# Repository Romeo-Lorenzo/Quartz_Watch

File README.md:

# DIY Quartz Watch project

## Introduction
This is my take at making my own quartz watch with a twist.
Driven by a PCF2003 chip from NXP as well as an STM32WB for bluetooth capability and controlling the subdial driving system in order to display data from the equipped sensors:
- Barometer
- Compass
- VBat
- Temp
- 1 cell lithium charge and discharge
- Very low power circuitry, 150nA continuous current consumption and 150mA with STM32 turned on. Designed to be equipped of two Airpods1 batteries in parralel for 50mAh total.

##Hardware:

  The hardware is divided into electrical and mecanical hardware

  ###Electrical:
  - 6 layer 36mm PCB board designed to replace original PCB from a Miyota 2035 movement. The PCB has two contact pads for two Miyota 2035 movements to drive both main and sub-dial. It is equipped with contact pads to ease programming of both the STM32 and the PCF 2003, most likely with pogo pin alignement 3D print to come.

  - TODO Monolayer PCB to mount as shield on Nucleo board equipped with OP Amp to be able to output the voltage necessary to program the PCF 2003. Will most likely be designed as a programming station and include the pogo pins and debug connector for programming the STM32 as well and be integrated with the forementioned 3d model to print.
 
  ###Mecanical:
  - Onshape designed 36mm watch case with high water resistance in mind, a water tight push button to control subdial and STM32 ON time.

Note that the Miyota 2035 movements will have to be modified, taking it apart and filing away the excess material on the bottom holding plate for the subdial movement is an easy fit and a tutorial on how to take apart and prepare the movements will be released.
The case is not yet finished but I estimate a 5 atm water tight watch, tolerances for CNC machinig will have to be tested. Crown will be a screw-in watertight type, a silicon membrane will ensure watertightness of the push button all the while allowing the inside barometer to read pressure, especially fun underwater.

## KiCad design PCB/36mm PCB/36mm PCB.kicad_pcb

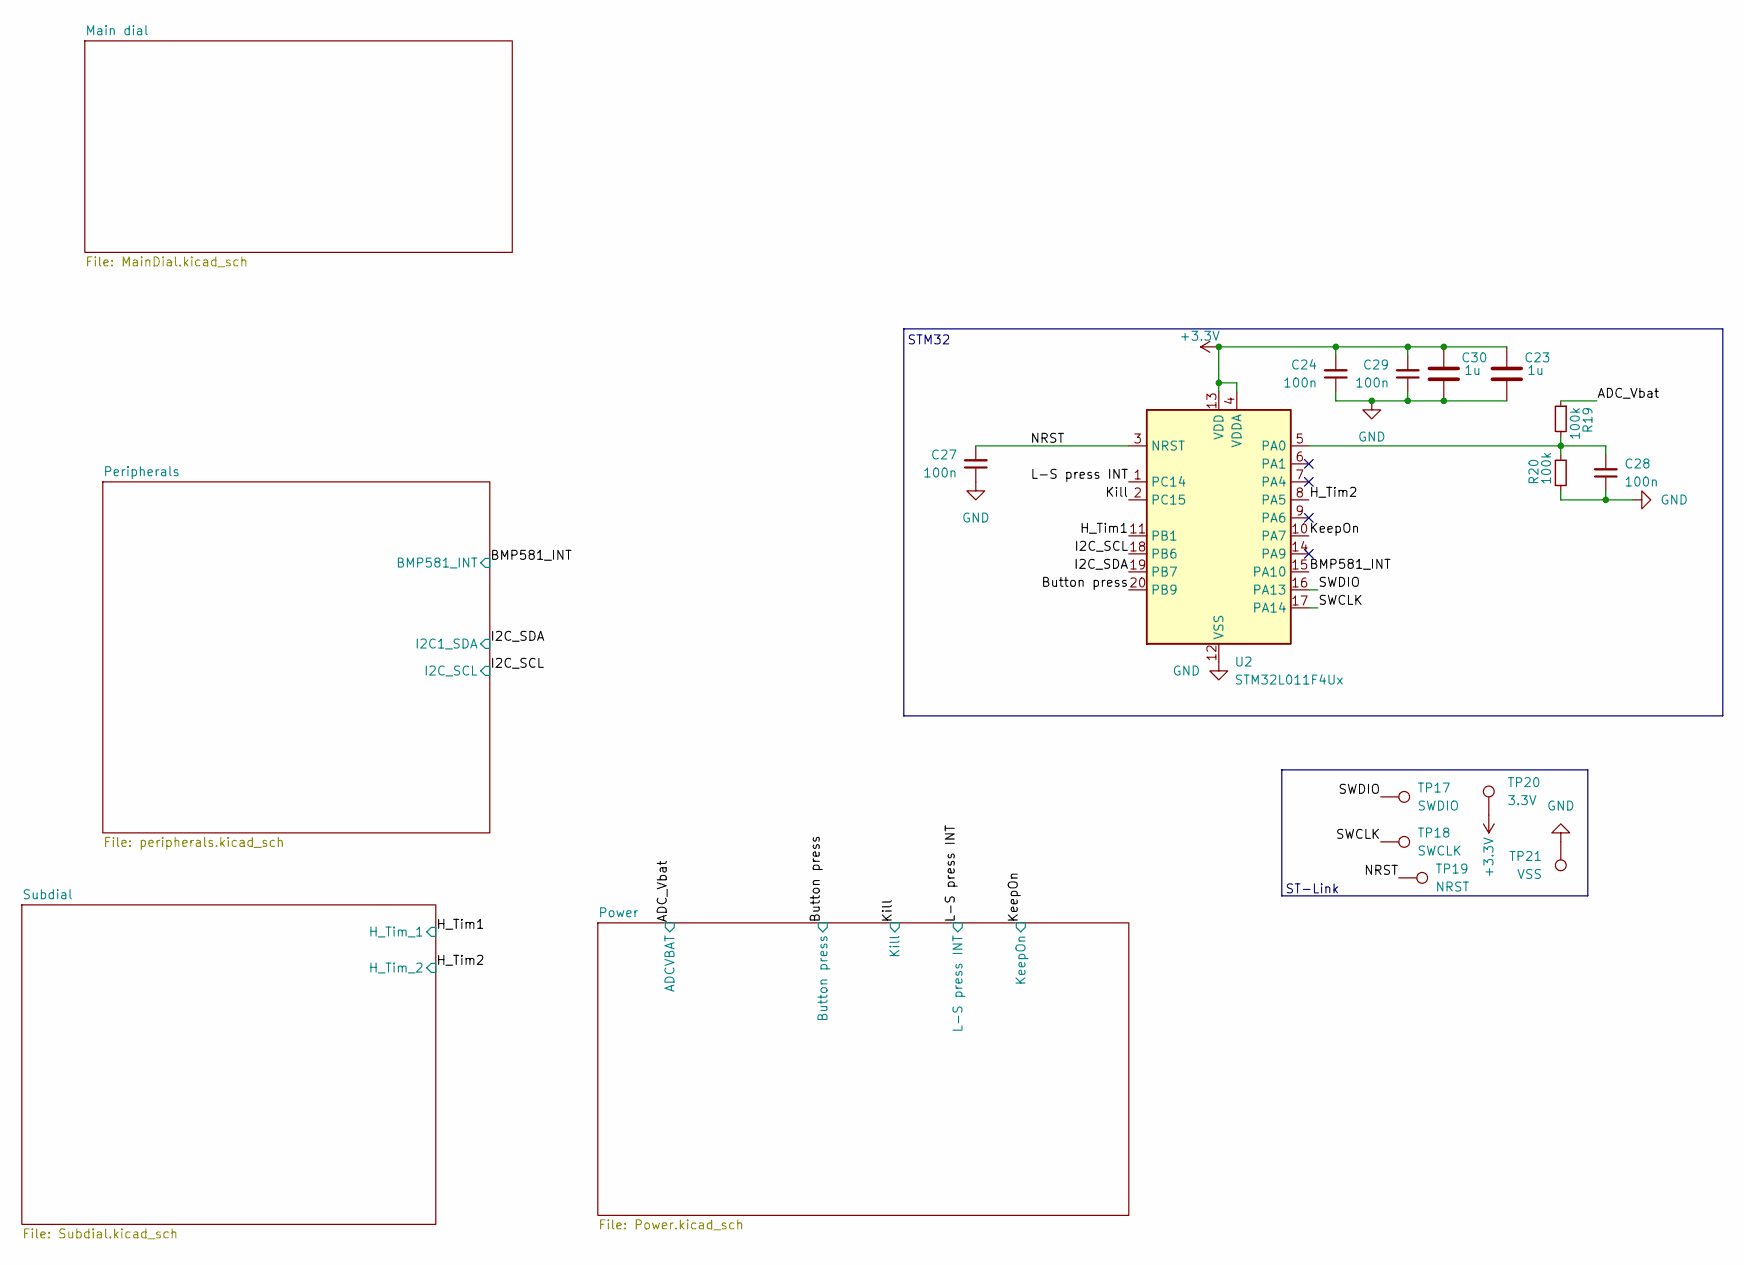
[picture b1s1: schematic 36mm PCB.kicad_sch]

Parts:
C23, C30: 1u; C_0402_1005Metric
C24, C27, C28, C29: 100n; C_0201_0603Metric
R19, R20: 100k; R_0201_0603Metric
TP17: SWDIO; Pogo pin 1x1
TP18: SWCLK; Pogo pin 1x1
TP19: NRST; Pogo pin 1x1
TP20: 3.3V; Pogo pin 1x1
TP21: VSS; Pogo pin 1x1
U2: STM32L011F4Ux; ST_UFQFPN-20_3x3mm_P0.5mm

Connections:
+3.3V: C23.1, C24.2, C29.2, C30.1, TP20.1, U2.4 (VDDA), U2.13 (VDD); also elsewhere on the board
+3V0: R19.1; also elsewhere on the board
/BMP581_INT: U2.15 (PA10); also elsewhere on the board
/Button press: U2.20 (PB9); also elsewhere on the board
/H_Tim1: U2.11 (PB1); also elsewhere on the board
/H_Tim2: U2.8 (PA5); also elsewhere on the board
/I2C_SCL: U2.18 (PB6); also elsewhere on the board
/I2C_SDA: U2.19 (PB7); also elsewhere on the board
/KeepOn: U2.10 (PA7); also elsewhere on the board
/Kill: U2.2 (PC15); also elsewhere on the board
/L-S press INT: U2.1 (PC14); also elsewhere on the board
/NRST: C27.2, TP19.1, U2.3 (NRST)
/SWCLK: TP18.1, U2.17 (PA14)
/SWDIO: TP17.1, U2.16 (PA13)
GND: C23.2, C24.1, C27.1, C28.1, C29.1, C30.2, R20.1, TP21.1, U2.12 (VSS); also elsewhere on the board
unnamed: C28.2, R19.2, R20.2, U2.5 (PA0)

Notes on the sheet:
ST-Link
STM32

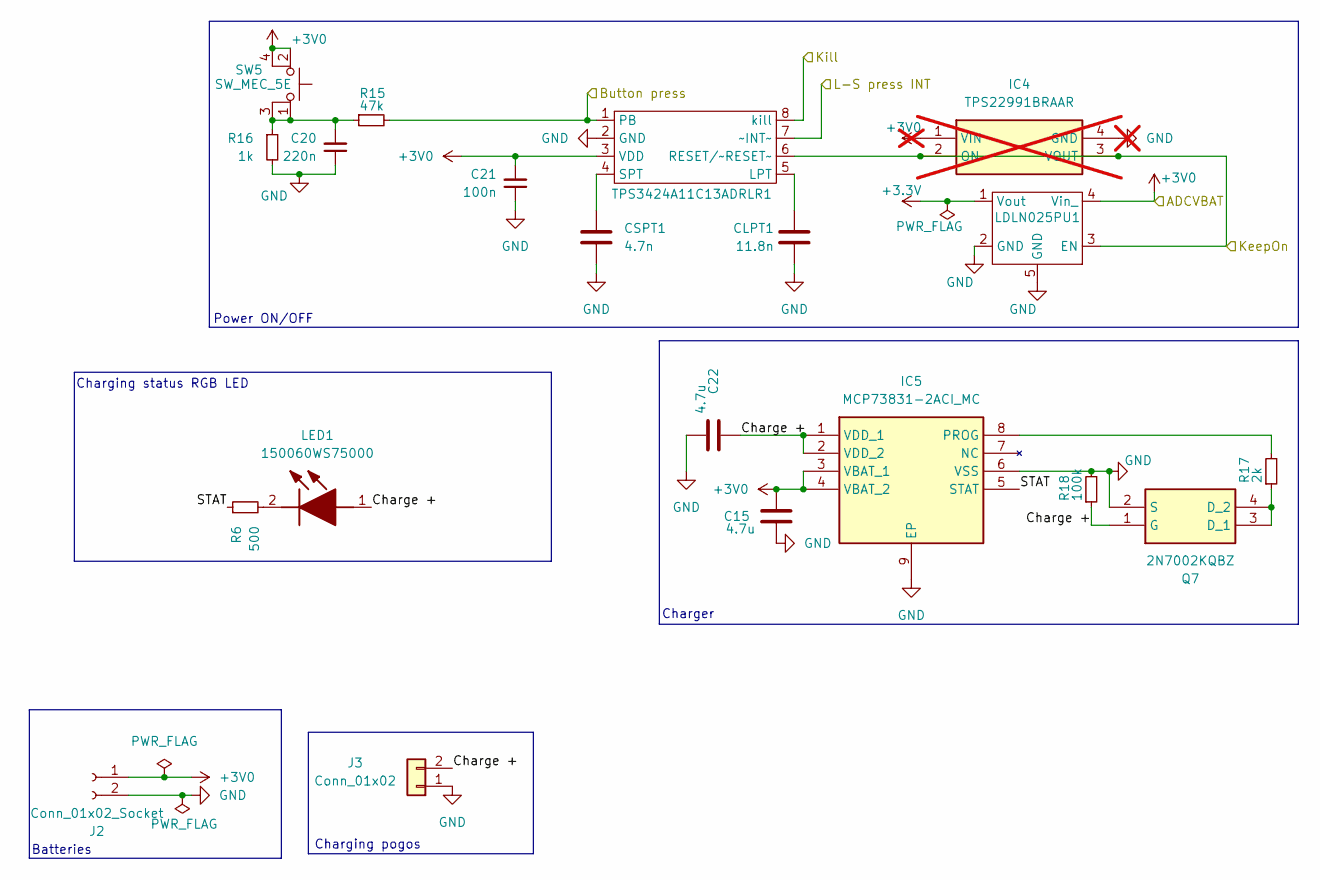
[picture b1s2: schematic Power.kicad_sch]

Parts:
C15, C22: 4.7u; C_0402_1005Metric
C20: 220n; C_0201_0603Metric
C21: 100n; C_0201_0603Metric
CLPT1: 11.8n; C_0402_1005Metric
CSPT1: 4.7n; C_0402_1005Metric
IC4: TPS22991BRAAR; Manufacturer_Part_Number TPS22991BRAAR; Mouser Part Number 595-TPS22991BRAAR; not fitted
IC5: MCP73831-2ACI_MC; SON50P300X200X100-9N-D; Manufacturer_Part_Number MCP73831-2ACI/MC; Mouser Part Number 579-MCP73831-2ACI/MC
J2: Conn_01x02_Socket; Battery 36mm watch
J3: Conn_01x02; Battery pogo pins
LDLN025PU1: OnSemi_XDFN4-1EP_1.0x1.0mm_EP0.52x0.52mm
LED1: 150060WS75000; Manufacturer_Part_Number 150060WS75000; Mouser Part Number 710-150060WS75000
Q7: 2N7002KQBZ; Manufacturer_Part_Number 2N7002KQBZ; Mouser Part Number 771-2N7002KQBZ
R6: 500; R_0201_0603Metric
R15: 47k; R_0201_0603Metric
R16: 1k; R_0201_0603Metric
R17: 2k; R_0201_0603Metric
R18: 100k; R_0201_0603Metric
SW5: SW_MEC_5E; Wurth side button 434331013822
TPS3424A11C13ADRLR1: SOT-583-8

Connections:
+3.3V: LDLN025PU1.1 (Vout); also elsewhere on the board
+3V0: C15.1, C21.2, IC4.1 (VIN), IC5.3 (VBAT_1), IC5.4 (VBAT_2), J2.1, LDLN025PU1.4 (Vin_), SW5.2, SW5.4, TPS3424A11C13ADRLR1.3 (VDD); also elsewhere on the board
/Button press: R15.2, TPS3424A11C13ADRLR1.1 (PB); also elsewhere on the board
/KeepOn: IC4.2 (ON), IC4.3 (VOUT), LDLN025PU1.3 (EN), TPS3424A11C13ADRLR1.6 (RESET/~RESET~); also elsewhere on the board
/Kill: TPS3424A11C13ADRLR1.8 (kill); also elsewhere on the board
/L-S press INT: TPS3424A11C13ADRLR1.7 (~INT~); also elsewhere on the board
/Power/Charge +: C22.1, IC5.1 (VDD_1), IC5.2 (VDD_2), J3.2, LED1.1 (A), Q7.1 (G), R18.1
/Power/STAT: IC5.5 (STAT), R6.1
GND: C15.2, C20.1, C21.1, C22.2, CLPT1.1, CSPT1.1, IC4.4 (GND), IC5.6 (VSS), IC5.9 (EP), J2.2, J3.1, LDLN025PU1.2 (GND), LDLN025PU1.5 (GND), Q7.2 (S), R16.2, R18.2, TPS3424A11C13ADRLR1.2 (GND); also elsewhere on the board
unnamed: C20.2, R15.1, R16.1, SW5.1, SW5.3
unnamed: IC5.8 (PROG), R17.2
unnamed: LED1.2 (K), R6.2
unnamed: Q7.3 (D_1), Q7.4 (D_2), R17.1
unnamed: CLPT1.2, TPS3424A11C13ADRLR1.5 (LPT)
unnamed: CSPT1.2, TPS3424A11C13ADRLR1.4 (SPT)

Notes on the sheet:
Charging pogos
Charging status RGB LED
Charger
Batteries
Power ON/OFF

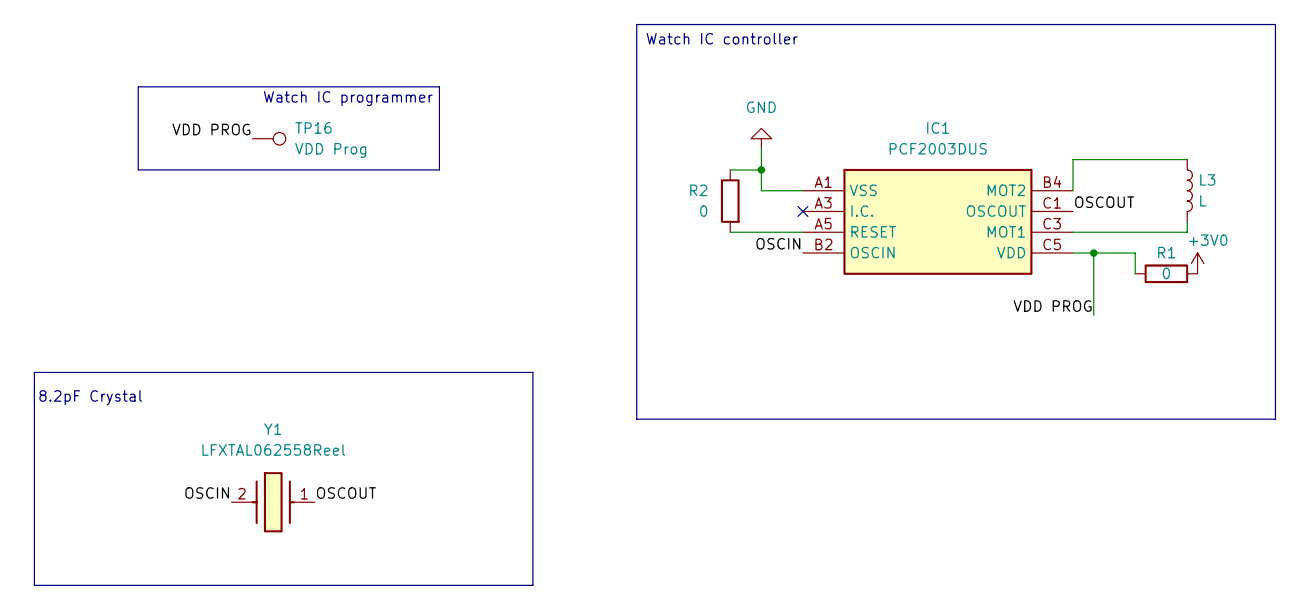
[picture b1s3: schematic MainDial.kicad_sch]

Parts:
IC1: PCF2003DUS; Manufacturer_Part_Number PCF2003DUS
L3: L; Miyota 2035
R1, R2: 0; R_0201_0603Metric
TP16: VDD Prog; Pogo pin 1x1
Y1: LFXTAL062558Reel; Manufacturer_Part_Number LFXTAL062558Reel; Mouser Part Number 449-LFXTAL062558REEL

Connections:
+3V0: R1.2; also elsewhere on the board
/Main dial/OSCIN: IC1.B2 (OSCIN), Y1.2 (CRYSTAL_2)
/Main dial/OSCOUT: IC1.C1 (OSCOUT), Y1.1
/Main dial/VDD PROG: IC1.C5 (VDD), R1.1, TP16.1
GND: IC1.A1 (VSS), R2.1; also elsewhere on the board
unnamed: IC1.C3 (MOT1), L3.2
unnamed: IC1.B4 (MOT2), L3.1
unnamed: IC1.A5 (RESET), R2.2

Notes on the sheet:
Watch IC controller
Watch IC programmer
8.2pF Crystal

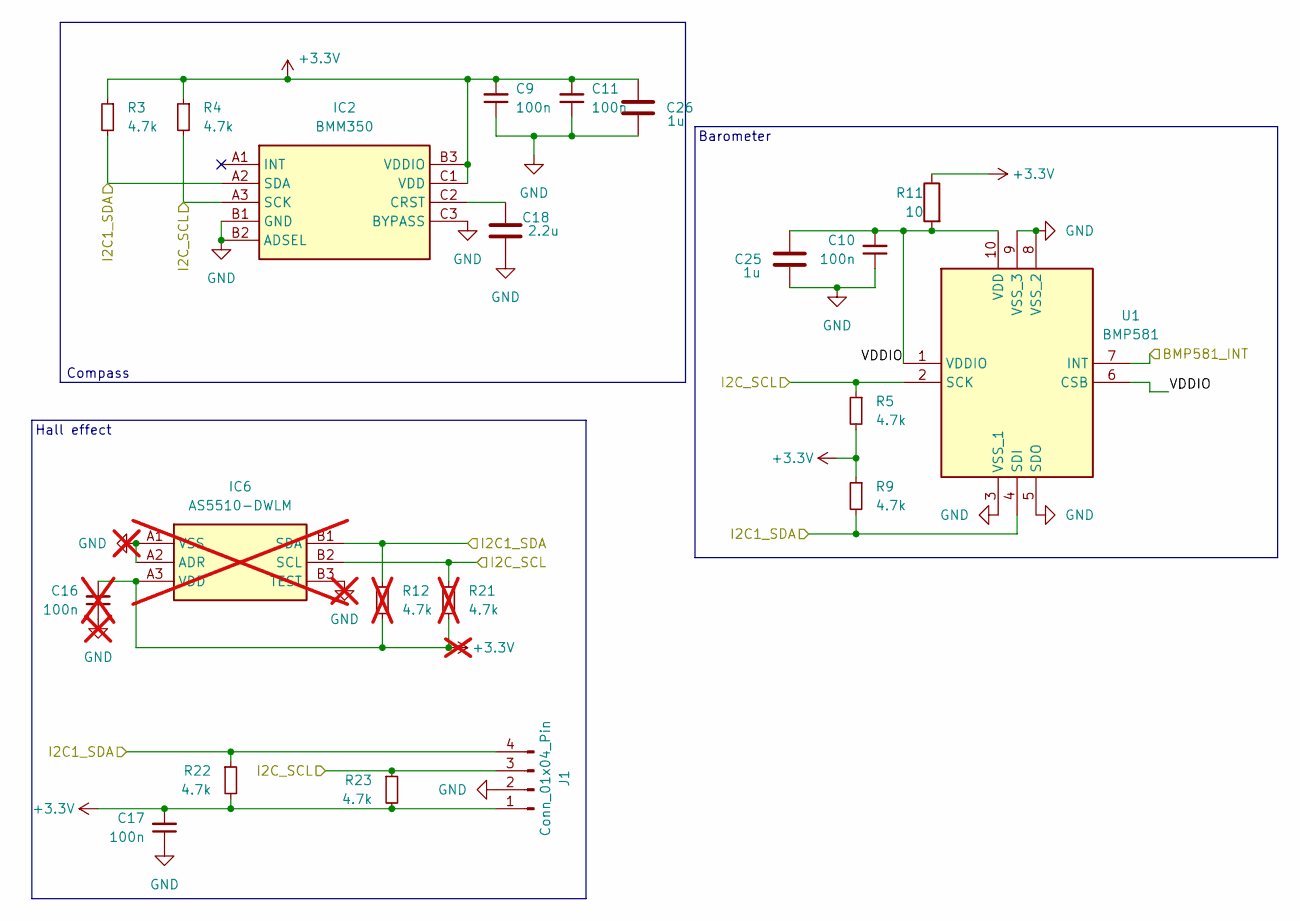
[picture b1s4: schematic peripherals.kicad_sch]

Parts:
C9, C10, C11, C17: 100n; C_0201_0603Metric
C16: 100n; C_0201_0603Metric; not fitted
C18: 2.2u; C_0402_1005Metric
C25, C26: 1u; C_0402_1005Metric
IC2: BMM350; BGA9C40P3X3_128X128X54; Mouser Part Number 262-BMM350
IC6: AS5510-DWLM; BGA6C40P3X2_138X102X63; Manufacturer_Part_Number AS5510-DWLM; Mouser Part Number 985-AS5510-DWLM; not fitted
J1: Conn_01x04_Pin; Hall effect
R3, R4, R5, R9, R22, R23: 4.7k; R_0201_0603Metric
R11: 10; R_0402_1005Metric
R12, R21: 4.7k; R_0201_0603Metric; not fitted
U1: BMP581; Manufacturer_Part_Number BMP581; Mouser Part Number 262-BMP581

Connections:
+3.3V: C9.2, C11.2, C16.2, C17.2, C26.1, IC2.B3 (VDDIO), IC2.C1 (VDD), IC6.A3 (VDD), J1.1, R3.1, R4.1, R5.2, R9.1, R11.1, R12.2, R21.2, R22.2, R23.2; also elsewhere on the board
/BMP581_INT: U1.7 (INT); also elsewhere on the board
/I2C_SCL: IC2.A3 (SCK), IC6.B2 (SCL), J1.3, R4.2, R5.1, R21.1, R23.1, U1.2 (SCK); also elsewhere on the board
/I2C_SDA: IC2.A2 (SDA), IC6.B1 (SDA), J1.4, R3.2, R9.2, R12.1, R22.1, U1.4 (SDI); also elsewhere on the board
/Peripherals/VDDIO: C10.2, C25.1, R11.2, U1.1 (VDDIO), U1.6 (CSB), U1.10 (VDD)
GND: C9.1, C10.1, C11.1, C16.1, C17.1, C18.2, C25.2, C26.2, IC2.B1 (GND), IC2.B2 (ADSEL), IC2.C3 (BYPASS), IC6.A1 (VSS), IC6.A2 (ADR), IC6.B3 (TEST), J1.2, U1.3 (VSS_1), U1.5 (SDO), U1.8 (VSS_2), U1.9 (VSS_3); also elsewhere on the board
unnamed: C18.1, IC2.C2 (CRST)

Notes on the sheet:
Barometer
Compass
Hall effect

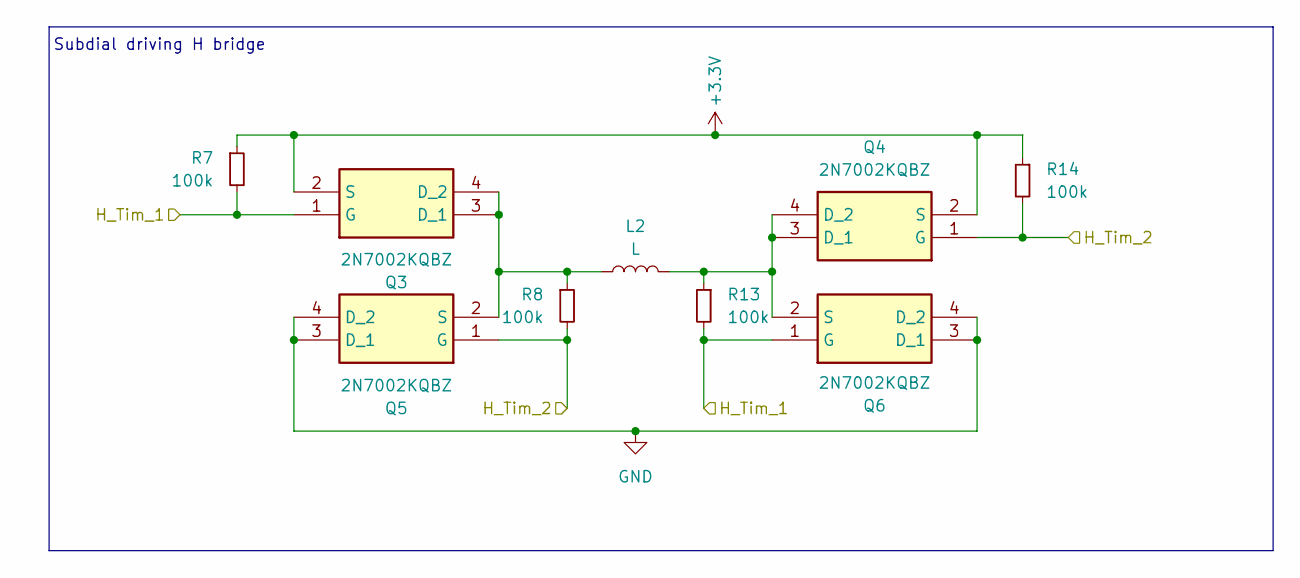
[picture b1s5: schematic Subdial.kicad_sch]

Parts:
L2: L; Miyota 2035
Q3, Q4, Q5, Q6: 2N7002KQBZ; Manufacturer_Part_Number 2N7002KQBZ; Mouser Part Number 771-2N7002KQBZ
R7, R8, R13, R14: 100k; R_0201_0603Metric

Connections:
+3.3V: Q3.2 (S), Q4.2 (S), R7.1, R14.1; also elsewhere on the board
/H_Tim1: Q3.1 (G), Q6.1 (G), R7.2, R13.2; also elsewhere on the board
/H_Tim2: Q4.1 (G), Q5.1 (G), R8.2, R14.2; also elsewhere on the board
GND: Q5.3 (D_1), Q5.4 (D_2), Q6.3 (D_1), Q6.4 (D_2); also elsewhere on the board
unnamed: L2.1, Q3.3 (D_1), Q3.4 (D_2), Q5.2 (S), R8.1
unnamed: L2.2, Q4.3 (D_1), Q4.4 (D_2), Q6.2 (S), R13.1

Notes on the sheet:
Subdial driving H bridge

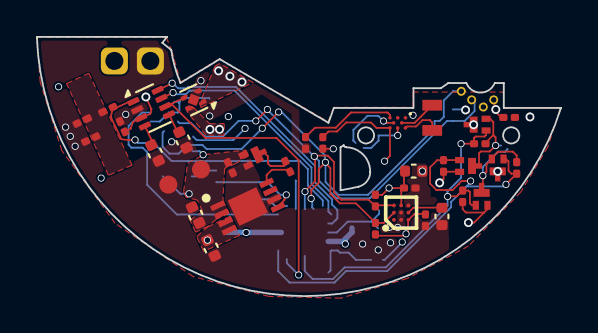
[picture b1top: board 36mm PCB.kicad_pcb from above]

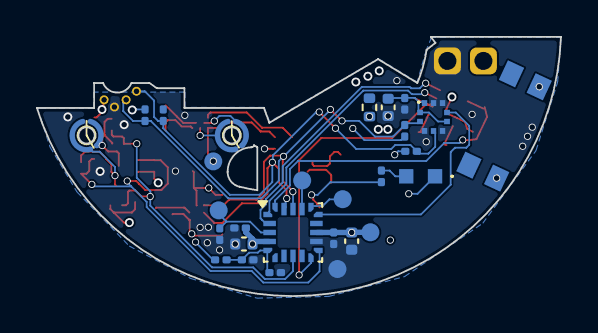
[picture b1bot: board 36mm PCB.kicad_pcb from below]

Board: 6 copper layers, 29.1 x 14.4 mm, 65 parts (28 on the bottom side), 34 nets.

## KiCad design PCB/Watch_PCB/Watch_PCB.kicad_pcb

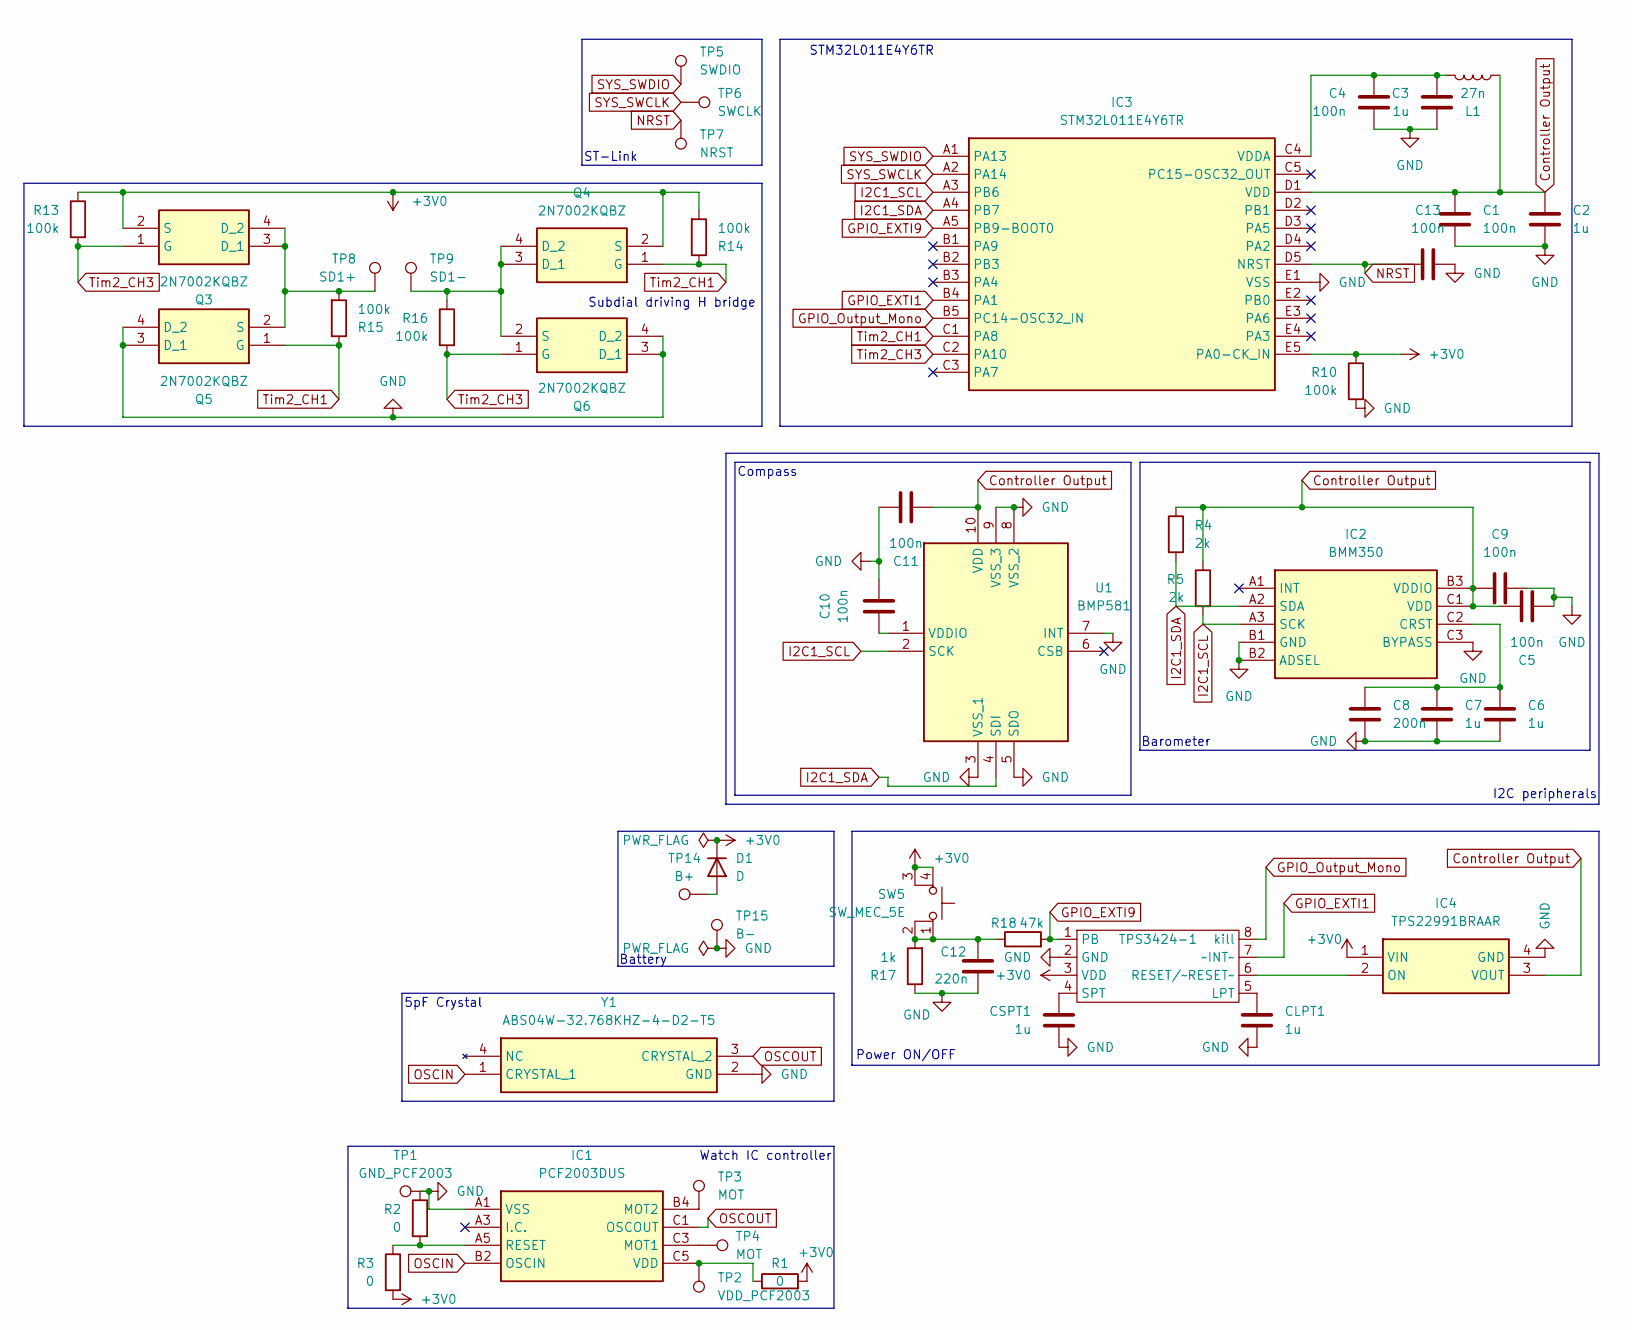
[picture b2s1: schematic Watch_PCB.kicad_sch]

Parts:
C1, C4, C5, C9, C10, C11, C13: 100n; C_0201_0603Metric
C2, C3, C6, C7: 1u; C_0201_0603Metric
C8: 200n; C_0201_0603Metric
C12: 220n; C_0201_0603Metric
CLPT1: 1u; C_0201_0603Metric
CSPT1: 1u; C_0201_0603Metric
D1: D; D_0201_0603Metric
IC1: PCF2003DUS; Manufacturer_Part_Number PCF2003DUS
IC2: BMM350; BGA9C40P3X3_128X128X54; Mouser Part Number 262-BMM350
IC3: STM32L011E4Y6TR; BGA25C40P5X5_213X207X58; Manufacturer_Part_Number STM32L011E4Y6TR; Mouser Part Number 511-STM32L011E4Y6TR
IC4: TPS22991BRAAR; Manufacturer_Part_Number TPS22991BRAAR; Mouser Part Number 595-TPS22991BRAAR
L1: 27n; L_0201_0603Metric
Q3, Q4, Q5, Q6: 2N7002KQBZ; Manufacturer_Part_Number 2N7002KQBZ; Mouser Part Number 771-2N7002KQBZ
R1, R2, R3: 0; R_0201_0603Metric
R4, R5: 2k; R_0201_0603Metric
R10, R13, R14, R15, R16: 100k; R_0201_0603Metric
R17: 1k; R_0201_0603Metric
R18: 47k; R_0201_0603Metric
SW5: SW_MEC_5E; Wurth side button 434331013822
TP1: GND_PCF2003; TestPoint_Pad_D1.0mm
TP2: VDD_PCF2003; TestPoint_Pad_D1.0mm
TP3, TP4: MOT; TestPoint_Pad_D1.0mm
TP5: SWDIO; TestPoint_Pad_D1.0mm
TP6: SWCLK; TestPoint_Pad_D1.0mm
TP7: NRST; TestPoint_Pad_D1.0mm
TP8: SD1+; TestPoint_Pad_D1.0mm
TP9: SD1-; TestPoint_Pad_D1.0mm
TP14: B+; TestPoint_Pad_D1.0mm
TP15: B-; TestPoint_Pad_D1.0mm
TPS3424-1: SOT-583-8
U1: BMP581; Manufacturer_Part_Number BMP581; Mouser Part Number 262-BMP581
Y1: ABS04W-32.768KHZ-4-D2-T5; ABS04W32768KHZ4D2T5; Manufacturer_Part_Number ABS04W-32.768KHZ-4-D2-T5; Mouser Part Number 815-04W-32.768-4-D2T

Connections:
+3V0: D1.1 (K), IC3.E5 (PA0-CK_IN), IC4.1 (VIN), Q3.2 (S), Q4.2 (S), R1.2, R3.2, R10.1, R13.1, R14.2, SW5.3 (K), SW5.4 (A), TPS3424-1.3 (VDD)
Controller Output: C1.2, C2.2, C5.1, C9.1, C11.2, IC2.B3 (VDDIO), IC2.C1 (VDD), IC3.D1 (VDD), IC4.3 (VOUT), L1.1, R4.1, R5.1, U1.10 (VDD)
GND: C1.1, C2.1, C3.1, C4.1, C5.2, C6.2, C7.2, C8.2, C9.2, C10.1, C11.1, C12.1, C13.2, CLPT1.1, CSPT1.1, IC1.A1 (VSS), IC2.B1 (GND), IC2.B2 (ADSEL), IC2.C3 (BYPASS), IC3.E1 (VSS), IC4.4 (GND), Q5.3 (D_1), Q5.4 (D_2), Q6.3 (D_1), Q6.4 (D_2), R2.1, R10.2, R17.1, TP1.1, TP15.1, TPS3424-1.2 (GND), U1.3 (VSS_1), U1.5 (SDO), U1.7 (INT), U1.8 (VSS_2), U1.9 (VSS_3), Y1.2 (GND), Y1.4 (NC)
GPIO_EXTI1: IC3.B4 (PA1), TPS3424-1.7 (~INT~)
GPIO_EXTI9: IC3.A5 (PB9-BOOT0), R18.2, TPS3424-1.1 (PB)
GPIO_Output_Mono: IC3.B5 (PC14-OSC32_IN), TPS3424-1.8 (kill)
I2C1_SCL: IC2.A3 (SCK), IC3.A3 (PB6), R5.2, U1.2 (SCK)
I2C1_SDA: IC2.A2 (SDA), IC3.A4 (PB7), R4.2, U1.4 (SDI)
NRST: C13.1, IC3.D5 (NRST), TP7.1
unnamed: C12.2, R17.2, R18.1, SW5.1, SW5.2
unnamed: D1.2 (A), TP14.1
unnamed 11: IC1.C3 (MOT1), TP4.1; also elsewhere on the board
unnamed 12: IC1.B4 (MOT2), TP3.1; also elsewhere on the board
unnamed: IC1.A5 (RESET), R2.2, R3.1
unnamed: IC1.C5 (VDD), R1.1, TP2.1
unnamed: C6.1, C7.1, C8.1, IC2.C2 (CRST)
unnamed: C3.2, C4.2, IC3.C4 (VDDA), L1.2
unnamed: IC4.2 (ON), TPS3424-1.6 (RESET/~RESET~)
unnamed 18: Q3.3 (D_1), Q3.4 (D_2), Q5.2 (S), R15.2, TP8.1; also elsewhere on the board
unnamed 19: Q4.3 (D_1), Q4.4 (D_2), Q6.2 (S), R16.1, TP9.1; also elsewhere on the board
unnamed: CLPT1.2, TPS3424-1.5 (LPT)
unnamed: CSPT1.2, TPS3424-1.4 (SPT)
unnamed: C10.2, U1.1 (VDDIO)
OSCIN: IC1.B2 (OSCIN), Y1.1 (CRYSTAL_1)
OSCOUT: IC1.C1 (OSCOUT), Y1.3 (CRYSTAL_2)
SYS_SWCLK: IC3.A2 (PA14), TP6.1
SYS_SWDIO: IC3.A1 (PA13), TP5.1
Tim2_CH1: IC3.C1 (PA8), Q4.1 (G), Q5.1 (G), R14.1, R15.1
Tim2_CH3: IC3.C2 (PA10), Q3.1 (G), Q6.1 (G), R13.2, R16.2

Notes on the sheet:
5pF Crystal
ST-Link
Power ON/OFF
Subdial driving H bridge
Compass
Watch IC controller
I2C peripherals
Barometer
Battery
STM32L011E4Y6TR

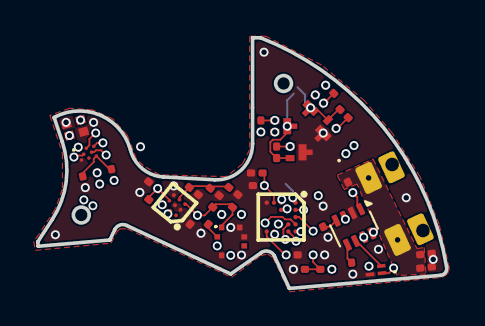
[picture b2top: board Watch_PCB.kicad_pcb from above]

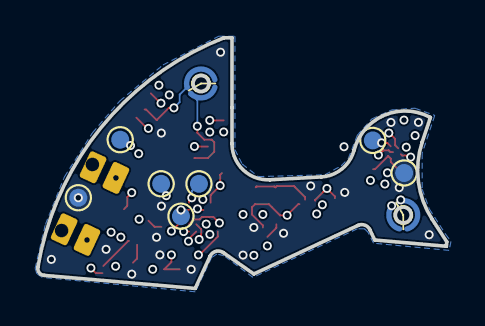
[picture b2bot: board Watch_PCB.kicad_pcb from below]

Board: 6 copper layers, 22.7 x 13.9 mm, 50 parts (9 on the bottom side), 29 nets.

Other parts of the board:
L2, L3: L; Miyota 2035

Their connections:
unnamed 11: L3.2; also elsewhere on the board
unnamed 12: L3.1; also elsewhere on the board
unnamed 18: L2.1; also elsewhere on the board
unnamed 19: L2.2; also elsewhere on the board

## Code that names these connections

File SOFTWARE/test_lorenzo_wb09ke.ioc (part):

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Mcu.Name=STM32WB09KEVx
Mcu.Package=VFQFPN32
Mcu.UserName=STM32WB09KEVx
PA0.Mode=I2C
PA0.Signal=I2C1_SCL
PA1.Mode=I2C
PA1.Signal=I2C1_SDA
PA2.Mode=Serial_Wire
PA2.Signal=DEBUG_SWDIO
PA3.Mode=Serial_Wire
PA3.Signal=DEBUG_SWCLK
PA8.GPIOParameters=GPIO_Label
PA8.GPIO_Label=EXTI_Baro
PA8.Signal=GPXTI8
PB0.Mode=VINM1
PB0.Signal=ADC1_VINM1
PB1.GPIOParameters=GPIO_Label
PB1.GPIO_Label=Button
PB1.Signal=GPXTI1
PB12.Mode=LSE-External-Oscillator
PB12.Signal=RCC_OSC32_OUT
PB13.Mode=LSE-External-Oscillator
PB13.Signal=RCC_OSC32_IN
PB14.GPIOParameters=GPIO_Label
PB14.GPIO_Label=H_on_GPIO
PB14.Signal=GPIO_Output
PB2.GPIOParameters=GPIO_Label
PB2.GPIO_Label=KeepOn
PB2.Signal=GPIO_Output
PB3.GPIOParameters=GPIO_Label
PB3.GPIO_Label=Kill
PB3.Signal=GPIO_Output
PB4.GPIOParameters=GPIO_Label
PB4.GPIO_Label=EXTI_LS_Press
PB4.Signal=GPXTI4
PB5.GPIOParameters=GPIO_Label
PB5.GPIO_Label=PCF2003_Reset
PB5.Signal=GPIO_Output
PB6.Signal=S_TIM2_CH1
PB7.Signal=S_TIM2_CH2
RCC.HSE_VALUE=32000000
board=custom

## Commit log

2025-03-18 Programming board
2025-06-22 Watch PCB schema
    Watch PCB schematictic
2025-06-22 added debounce on switch
2025-06-22 pcb outline
2025-06-30 pcb layout
    pcb layout
2025-07-27 PCB V1
    PCB V1 complete
2025-08-16 36mm pcb
2025-10-03 PCB 2.0
2025-10-03 Safety push
2025-10-03 Modifs Mathieu
2025-10-04 STM32 BLE + H chip
2025-10-22 Revise README with project overview and hardware specs
    Expanded project description and hardware details for the DIY Quartz Watch.
